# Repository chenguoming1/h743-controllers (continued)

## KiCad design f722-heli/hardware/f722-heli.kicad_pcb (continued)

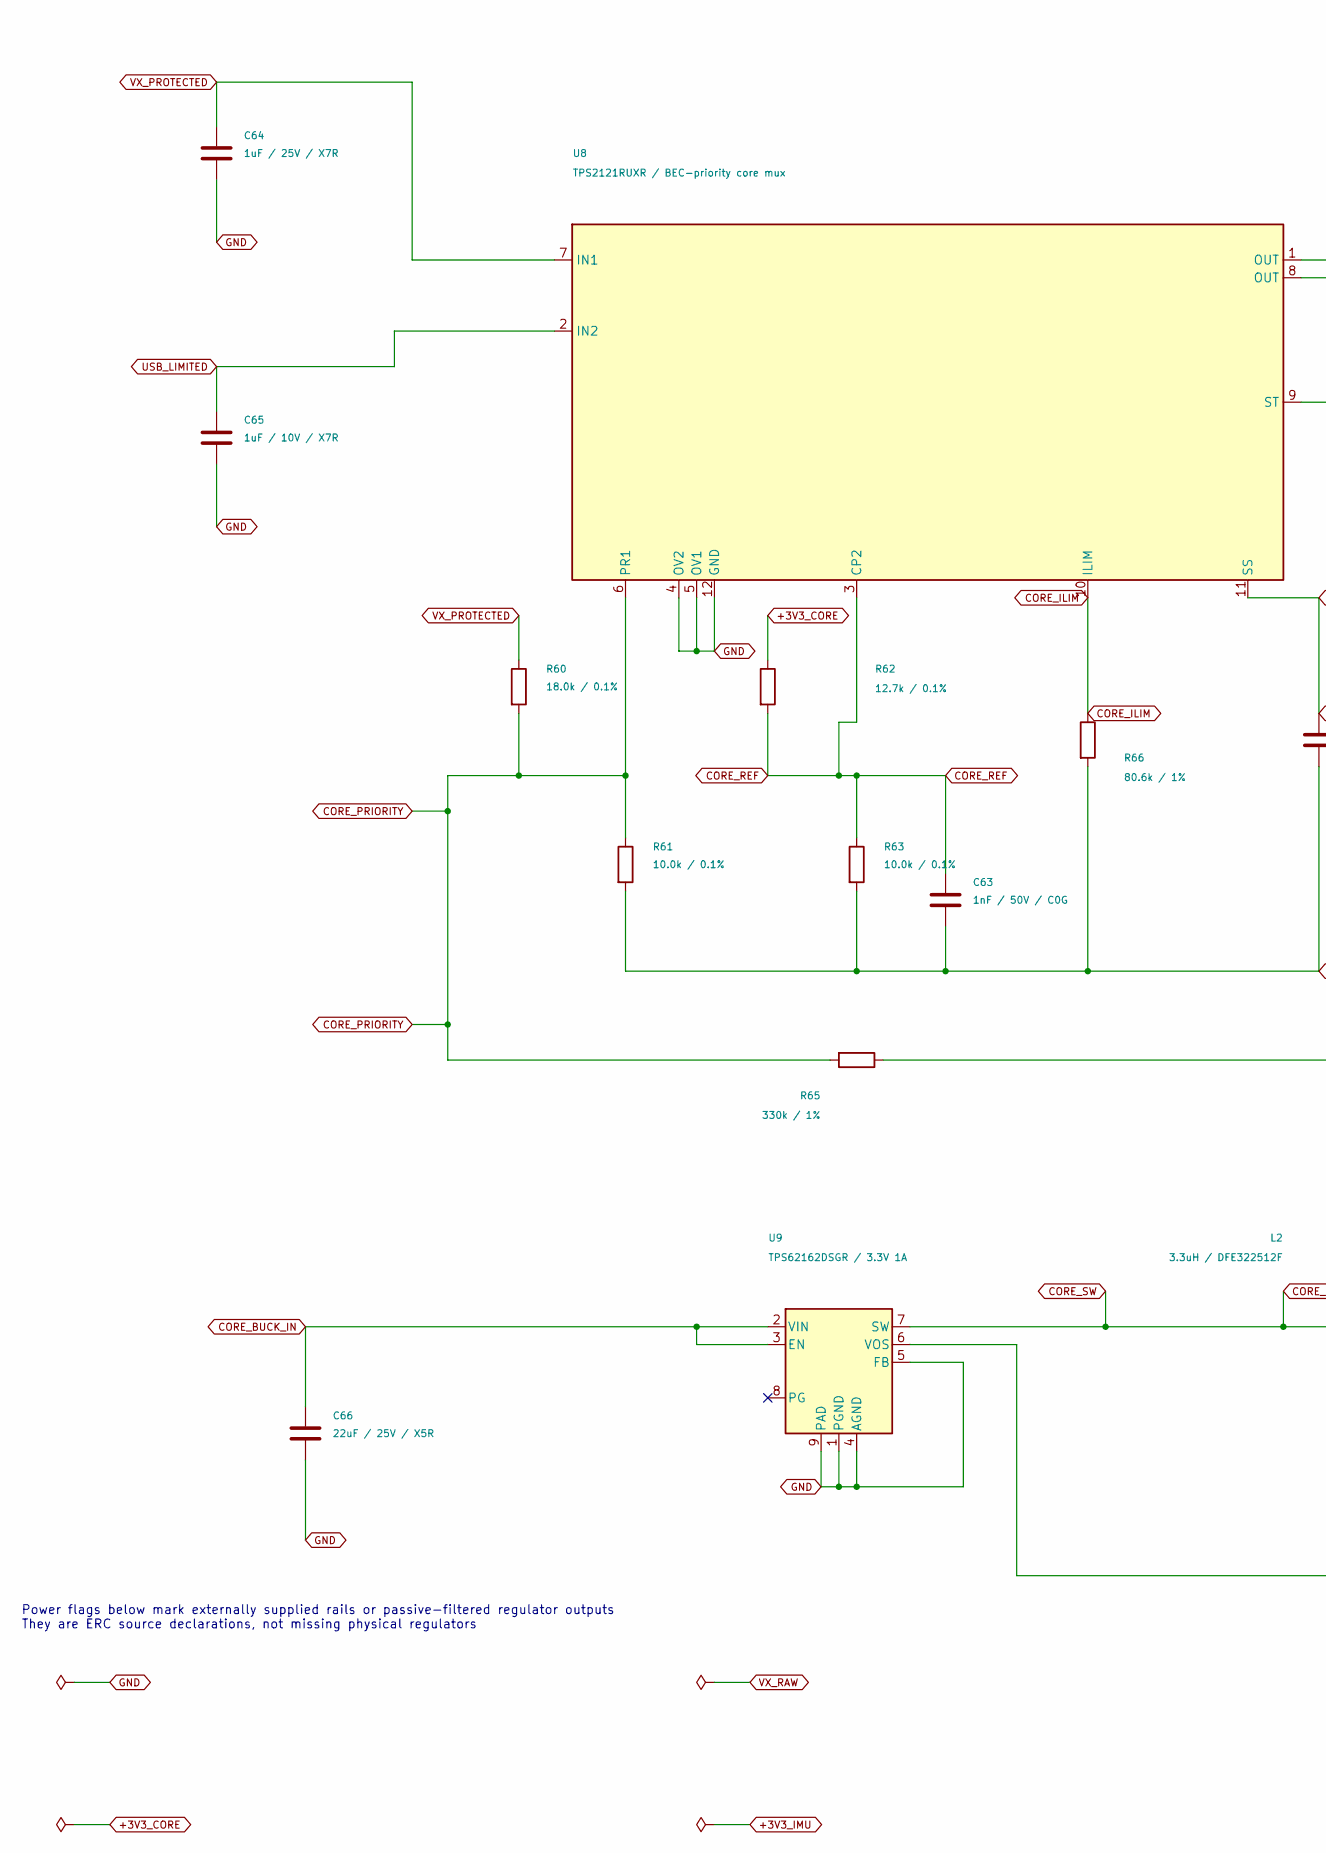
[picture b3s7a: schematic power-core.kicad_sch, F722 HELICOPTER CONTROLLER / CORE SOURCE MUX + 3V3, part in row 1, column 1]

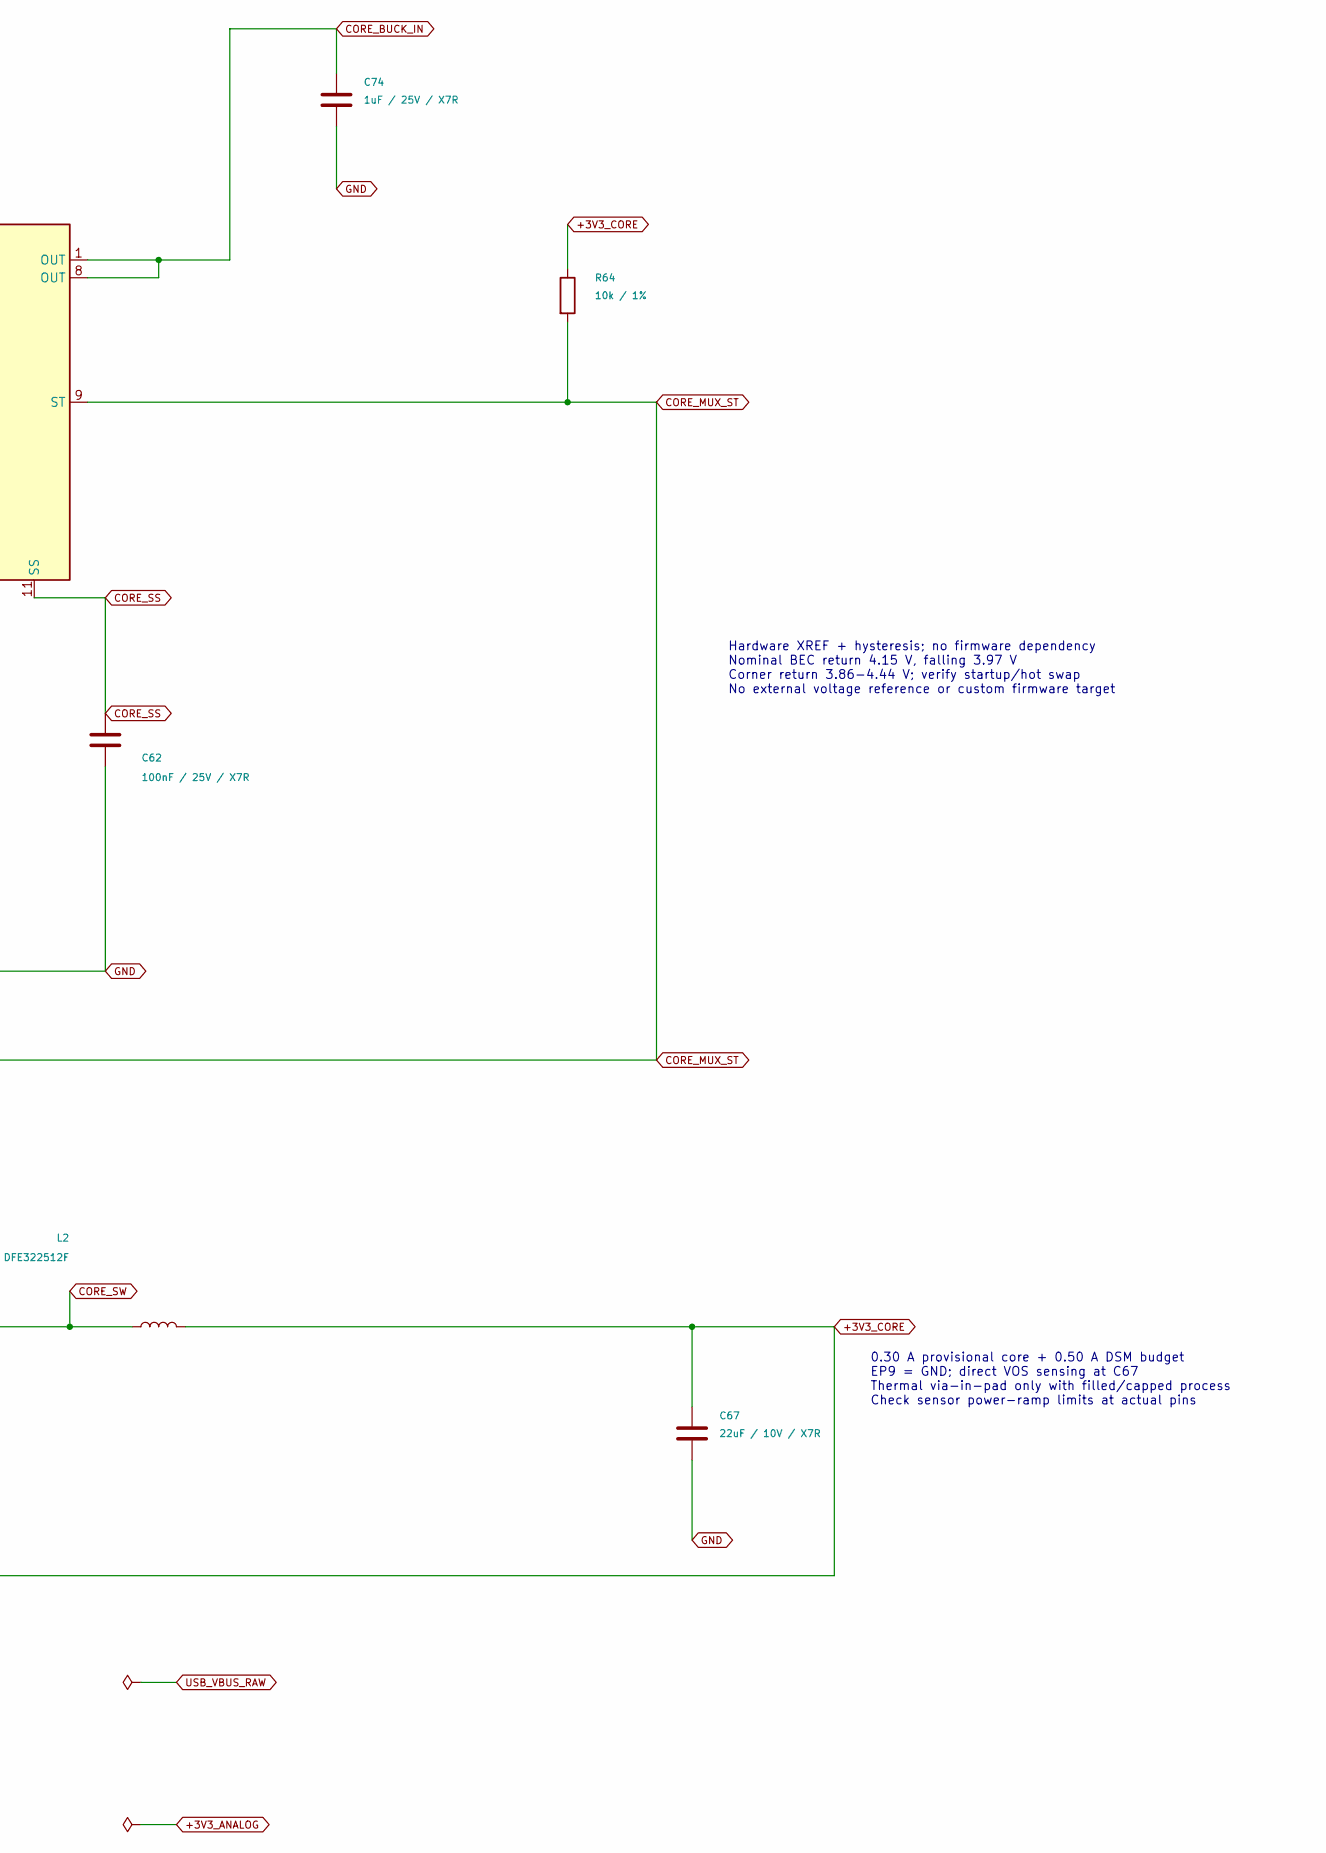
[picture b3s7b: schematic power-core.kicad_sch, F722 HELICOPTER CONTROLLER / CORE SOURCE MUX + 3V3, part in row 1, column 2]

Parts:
C62: 100nF / 25V / X7R; C_0402_1005Metric; MPN CL05B104KA5NNNC; LCSC C155422
C63: 1nF / 50V / C0G; C_0402_1005Metric; MPN CL05C102JB5NNNC; LCSC C307441
C64, C74: 1uF / 25V / X7R; C_0603_1608Metric; MPN CL10B105KA8NNNC; LCSC C29936
C65: 1uF / 10V / X7R; C_0603_1608Metric; MPN CL10B105KP8NNNC; LCSC C95843
C66: 22uF / 25V / X5R; C_0805_2012Metric; MPN GRM21BR61E226ME44L; LCSC C86816
C67: 22uF / 10V / X7R; C_0805_2012Metric; MPN GRM21BZ71A226ME15L; LCSC C907991
L2: 3.3uH / DFE322512F; Murata_DFE322512F; MPN DFE322512F-3R3M=P2; LCSC C3221010
R60: 18.0k / 0.1%; R_0402_1005Metric; MPN RT0402BRD0718KL; LCSC C852579
R61, R63: 10.0k / 0.1%; R_0402_1005Metric; MPN RT0402BRD0710KL; LCSC C190095
R62: 12.7k / 0.1%; R_0402_1005Metric; MPN RT0402BRD0712K7L; LCSC C852509
R64: 10k / 1%; R_0402_1005Metric; MPN 0402WGF1002TCE; LCSC C25744
R65: 330k / 1%; R_0402_1005Metric; MPN 0402WGF3303TCE; LCSC C25778
R66: 80.6k / 1%; R_0402_1005Metric; MPN 0402WGF8062TCE; LCSC C25921
U8: TPS2121RUXR / BEC-priority core mux; Texas_RUX0012A_TPS2121_2x2.5mm; MPN TPS2121RUXR; LCSC C485916
U9: TPS62162DSGR / 3.3V 1A; Texas_DSG0008A_TPS62162_2x2mm_EP0.9x1.6mm; MPN TPS62162DSGR; LCSC C40256

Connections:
+3V3_CORE: C67.1, L2.2, R62.1, R64.1, U9.6 (VOS); also elsewhere on the board
CORE_BUCK_IN: C66.1, C74.1, U8.1 (OUT), U8.8 (OUT), U9.2 (VIN), U9.3 (EN)
CORE_ILIM: R66.1, U8.10 (ILIM)
CORE_MUX_ST: R64.2, R65.1, U8.9 (ST)
CORE_PRIORITY: R60.2, R61.1, R65.2, U8.6 (PR1)
CORE_REF: C63.1, R62.2, R63.1, U8.3 (CP2)
CORE_SS: C62.1, U8.11 (SS)
CORE_SW: L2.1, U9.7 (SW)
GND: C62.2, C63.2, C64.2, C65.2, C66.2, C67.2, C74.2, R61.2, R63.2, R66.2, U8.4 (OV2), U8.5 (OV1), U8.12 (GND), U9.1 (PGND), U9.4 (AGND), U9.5 (FB), U9.9 (PAD); also elsewhere on the board
USB_LIMITED: C65.1, U8.2 (IN2); also elsewhere on the board
VX_PROTECTED: C64.1, R60.1, U8.7 (IN1); also elsewhere on the board

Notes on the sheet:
Hardware XREF + hysteresis; no firmware dependency Nominal BEC return 4.15 V, falling 3.97 V Corner return 3.86-4.44 V; verify startup/hot swap No external voltage reference or custom firmware target
0.30 A provisional core + 0.50 A DSM budget EP9 = GND; direct VOS sensing at C67 Thermal via-in-pad only with filled/capped process Check sensor power-ramp limits at actual pins
Power flags below mark externally supplied rails or passive-filtered regulator outputs They are ERC source declarations, not missing physical regulators

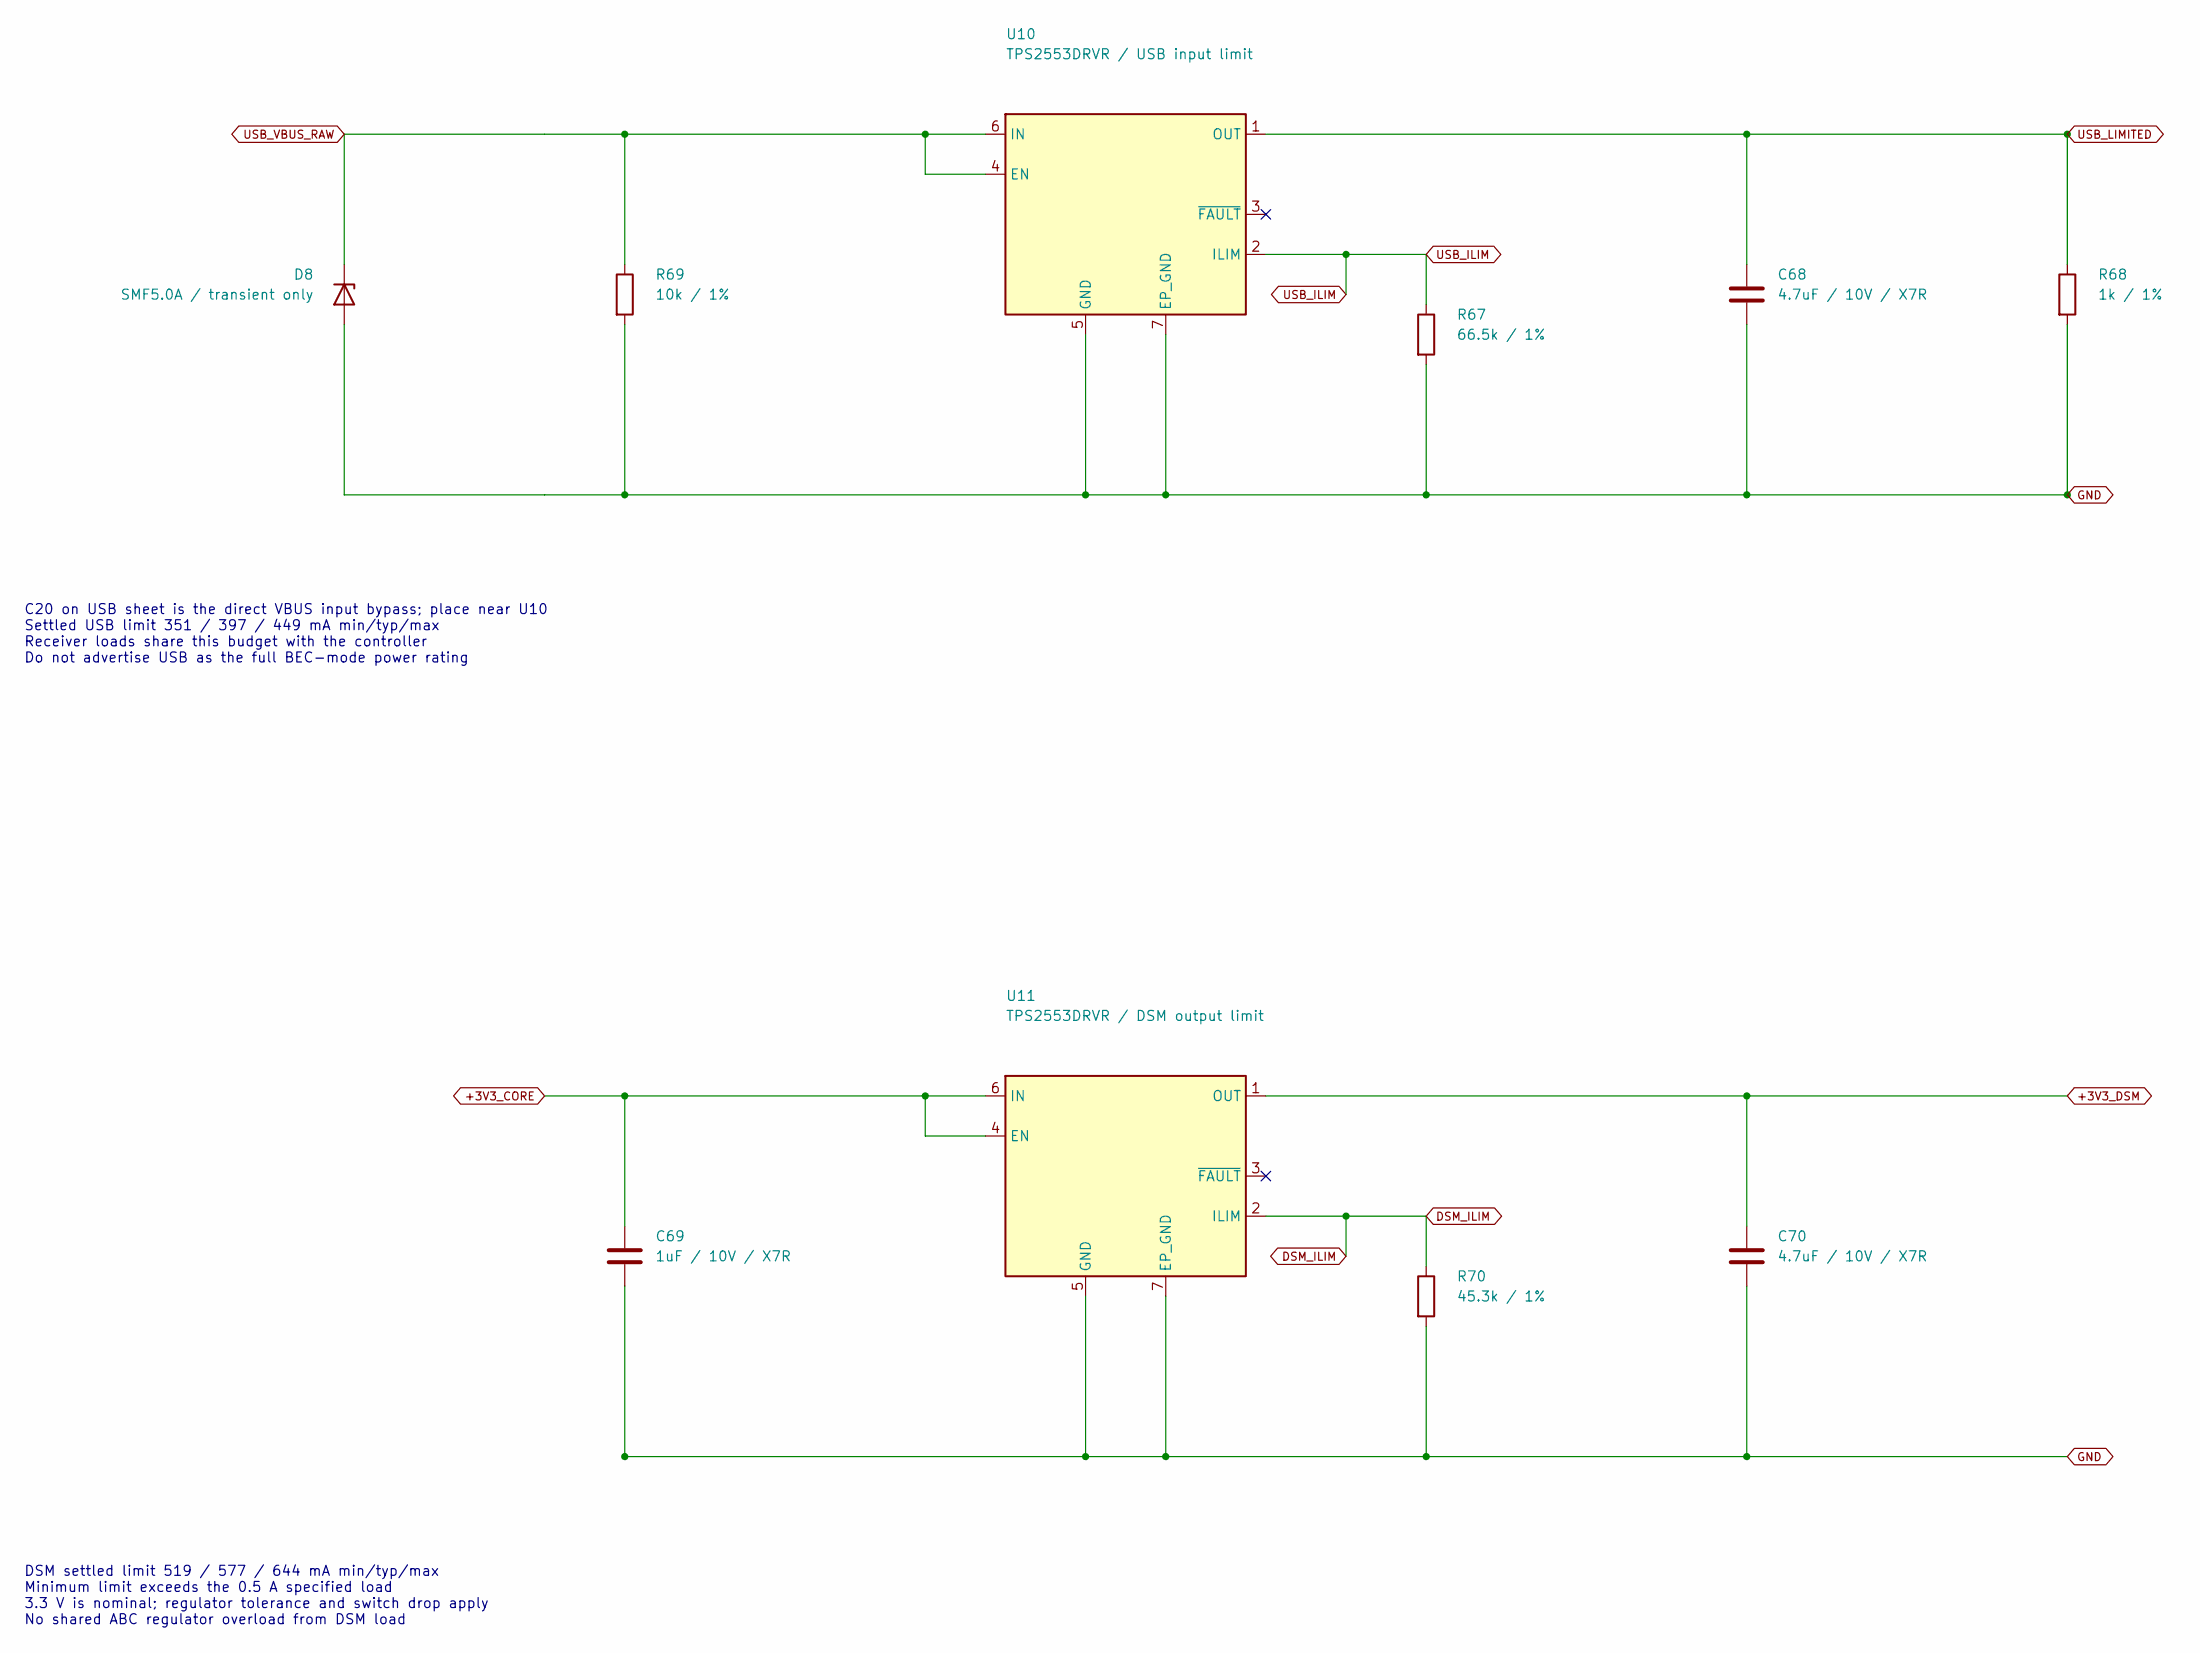
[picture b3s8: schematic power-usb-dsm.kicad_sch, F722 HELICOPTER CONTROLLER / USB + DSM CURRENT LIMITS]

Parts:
C68, C70: 4.7uF / 10V / X7R; C_0603_1608Metric; MPN GRM188Z71A475KE15D; LCSC C913474
C69: 1uF / 10V / X7R; C_0603_1608Metric; MPN CL10B105KP8NNNC; LCSC C95843
D8: SMF5.0A / transient only; Littelfuse_SMF_SOD123FL; MPN SMF5.0A; LCSC C151296
R67: 66.5k / 1%; R_0402_1005Metric; MPN 0402WGF6652TCE; LCSC C29381
R68: 1k / 1%; R_0402_1005Metric; MPN 0402WGF1001TCE; LCSC C11702
R69: 10k / 1%; R_0402_1005Metric; MPN 0402WGF1002TCE; LCSC C25744
R70: 45.3k / 1%; R_0402_1005Metric; MPN 0402WGF4532TCE; LCSC C26980
U10: TPS2553DRVR / USB input limit; Texas_DRV0006A_TPS2553_2x2mm_EP1x1.6mm; MPN TPS2553DRVR; LCSC C138719
U11: TPS2553DRVR / DSM output limit; Texas_DRV0006A_TPS2553_2x2mm_EP1x1.6mm; MPN TPS2553DRVR; LCSC C138719

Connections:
+3V3_CORE: C69.1, U11.4 (EN), U11.6 (IN); also elsewhere on the board
+3V3_DSM: C70.1, U11.1 (OUT); also elsewhere on the board
DSM_ILIM: R70.1, U11.2 (ILIM)
GND: C68.2, C69.2, C70.2, D8.2 (A), R67.2, R68.2, R69.2, R70.2, U10.5 (GND), U10.7 (EP_GND), U11.5 (GND), U11.7 (EP_GND); also elsewhere on the board
USB_ILIM: R67.1, U10.2 (ILIM)
USB_LIMITED: C68.1, R68.1, U10.1 (OUT); also elsewhere on the board
USB_VBUS_RAW: D8.1 (K), R69.1, U10.4 (EN), U10.6 (IN); also elsewhere on the board

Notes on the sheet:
C20 on USB sheet is the direct VBUS input bypass; place near U10 Settled USB limit 351 / 397 / 449 mA min/typ/max Receiver loads share this budget with the controller Do not advertise USB as the full BEC-mode power rating
DSM settled limit 519 / 577 / 644 mA min/typ/max Minimum limit exceeds the 0.5 A specified load 3.3 V is nominal; regulator tolerance and switch drop apply No shared ABC regulator overload from DSM load

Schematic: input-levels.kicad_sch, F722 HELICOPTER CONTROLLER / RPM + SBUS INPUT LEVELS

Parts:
Q1, Q2: BSS138LT1G; SOT-23; MPN BSS138LT1G; LCSC C82045
R36, R37: 4.7k / 1%; R_0402_1005Metric; MPN 0402WGF4701TCE; LCSC C25900
R39, R45: 220R / 1%; R_0402_1005Metric; MPN 0402WGF2200TCE; LCSC C25091
U16: PESD15VS2UT,215 / 15V ESD; SOT-23; MPN PESD15VS2UT,215; LCSC C282556

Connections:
+3V3_CORE: Q1.1 (G), Q2.1 (G), R36.1, R37.1; also elsewhere on the board
GND: U16.3 (COMMON_GND); also elsewhere on the board
RPM_HV: Q1.3 (D), U16.1 (LINE1); also elsewhere on the board
RPM_LV: Q1.2 (S), R36.2, R39.1
SBUS_HV: Q2.3 (D), U16.2 (LINE2); also elsewhere on the board
SBUS_LV: Q2.2 (S), R37.2, R45.1

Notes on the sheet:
External signal -> 470R on port sheet -> HV drain Gate = core supply; source pulled to the same core supply 220R then original MCU node, protected by U13 No fixed inverter; frequency/serial polarity is preserved Stock frequency-input pull-up never sees a VX-level high
Qualify real cable/device edges, startup and powered-off states No extra source capacitor fitted No claim of sustained negative-signal or wrong-output-wiring immunity ESC and tail bidirectional DShot paths remain unbuffered

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
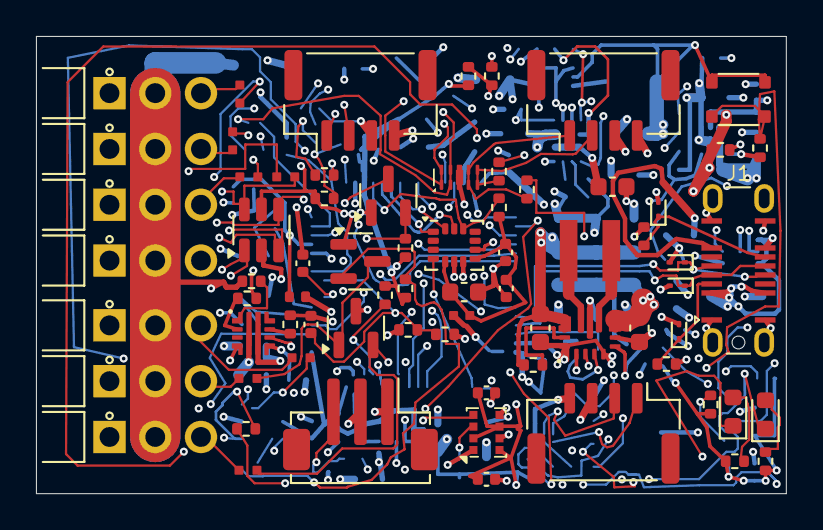
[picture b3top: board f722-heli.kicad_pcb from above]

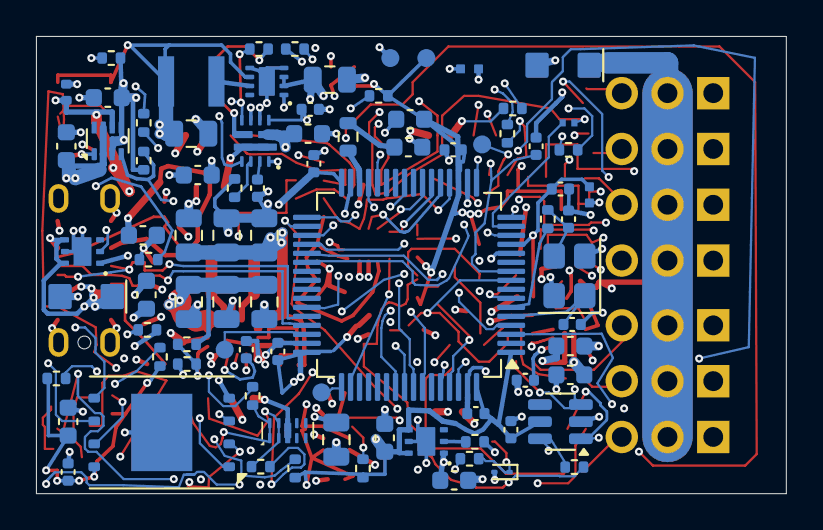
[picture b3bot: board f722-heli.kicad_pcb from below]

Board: 6 copper layers, 41.7 x 25.4 mm, 156 parts (84 on the bottom side), 95 nets.

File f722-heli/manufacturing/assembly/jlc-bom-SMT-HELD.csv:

Comment,Designator,Footprint,LCSC Part #
100nF / 16V / X7R,"C1,C2,C3,C4,C6,C9,C10,C12,C14,C16,C17,C58",F722_Heli:C_0402_1005Metric,C1525
4.7uF / 10V / X5R,C5,F722_Heli:C_0603_1608Metric,C1705
4.7uF / 10V / X7R,"C7,C61,C68,C70",F722_Heli:C_0603_1608Metric,C913474
2.2uF / 10V / X7R(Murata),"C8,C60",F722_Heli:Murata_GRM155Z71A225KE44_0402,C2999759
10nF / 16V / X7R,C11,F722_Heli:C_0402_1005Metric,C318577
2.2uF / 10V / X7R,C13,F722_Heli:C_0603_1608Metric,C100082
1uF / 10V / X7R,"C15,C59,C65,C69",F722_Heli:C_0603_1608Metric,C95843
15pF / 50V / C0G,"C18,C19",F722_Heli:C_0402_1005Metric,C86285
1uF / 16V / X7R,C20,F722_Heli:C_0603_1608Metric,C59782
220nF / 16V / X7R,"C30,C31",F722_Heli:C_0402_1005Metric,C16772
3.3nF / 50V / C0G,C50,F722_Heli:C_0402_1005Metric,C1518207
1uF / 25V / X7R,"C51,C52,C64,C74",F722_Heli:C_0603_1608Metric,C29936
22uF / 25V / X5R,"C53,C54,C66,C71",F722_Heli:C_0805_2012Metric,C86816
47uF / 10V / X5R,"C55,C56,C57,C75",F722_Heli:C_0805_2012Metric,C124129
100nF / 25V / X7R,C62,F722_Heli:C_0402_1005Metric,C155422
1nF / 50V / C0G,C63,F722_Heli:C_0402_1005Metric,C307441
22uF / 10V / X7R,C67,F722_Heli:C_0805_2012Metric,C907991
10uF / 25V / X5R / HF,"C72,C73",F722_Heli:C_0603_1608Metric,C386081
GREEN,D1,F722_Heli:LED_0603_1608Metric,C2289
RED,D2,F722_Heli:LED_0603_1608Metric,C2286
ESD9M5.0ST5G,"D3,D4,D5,D6,D7",F722_Heli:D_SOD-923,C242267
SMF5.0A / transient only,D8,F722_Heli:Littelfuse_SMF_SOD123FL,C151296
SMF15CA / bidirectional,D9,F722_Heli:Littelfuse_SMF_SOD123FL,C1851361
600R@100MHz / 0.3A,"FB1,FB2",F722_Heli:Murata_BLM15AG_0402,C76884
USB4145-03-0170-C,J1,F722_Heli:USB_C_Receptacle_GCT_USB4145-03-0170-C_16P_Vertical,C5181332
PORT A / JST GH,J9,F722_Heli:JST_GH_BM04B-GHS-TBT_1x04-1MP_P1.25mm_Vertical,C161692
PORT B / JST GH,J10,F722_Heli:JST_GH_BM04B-GHS-TBT_1x04-1MP_P1.25mm_Vertical,C161692
PORT C / JST GH,J11,F722_Heli:JST_GH_BM04B-GHS-TBT_1x04-1MP_P1.25mm_Vertical,C161692
DSM / JST ZH,J12,F722_Heli:JST_ZH_B3B-ZR-SM4-TF_1x03-1MP_P1.50mm_Vertical,C489717
1.5uH / XGL4020-152MEC,L1,F722_Heli:Coilcraft_XGL4020,C7417180
3.3uH / DFE322512F,L2,F722_Heli:Murata_DFE322512F,C3221010
BSS138LT1G,"Q1,Q2",F722_Heli:SOT-23,C82045
10k / 1%,"R1,R3,R4,R6,R64,R69",F722_Heli:R_0402_1005Metric,C25744
2.2k / 1%,"R2,R10,R11",F722_Heli:R_0402_1005Metric,C25879
10k / 1%,R5,F722_Heli:R_0402_1005Metric_R5_ClearPin1Silk,C25744
4.7k / 1%,"R7,R8,R36,R37",F722_Heli:R_0402_1005Metric,C25900
0R / drive tuning,R9,F722_Heli:R_0402_1005Metric,C17168
5.1k / 1%,"R14,R15",F722_Heli:R_0402_1005Metric,C25905
0.12R / 1% / VCAP ESR,R16,F722_Heli:R_Panasonic_ERJ3R_0603,C4059772
470R / 1% / 0.20W,"R20,R21,R22,R23,R24,R25,R26",F722_Heli:Panasonic_ERJPA2_0402,C427238
22R / 1%,"R30,R32,R33,R34,R35,R38",F722_Heli:R_0402_1005Metric,C25092
22R / 1%,R31,F722_YAGEO:R_0201_0603Metric_YAGEO_AC,C144830
220R / 1%,"R39,R45",F722_Heli:R_0402_1005Metric,C25091
105k / 0.1%,R40,F722_Heli:R_0402_1005Metric,C2984407
20.0k / 0.1%,R41,F722_Heli:R_0402_1005Metric,C705630
68.0k / 0.1%,R42,F722_Heli:R_0402_1005Metric,C5266108
16.0k / 0.1%,"R43,R44",F722_Heli:R_0402_1005Metric,C513647
1.5M / 1%,R50,F722_Heli:R_0402_1005Metric,C22276
390k / 1%,R51,F722_Heli:R_0402_1005Metric,C25782
750R / 1%,R52,F722_Heli:R_0402_1005Metric,C25132
4.7k / 1%,R53,F722_Heli:Panasonic_ERJPA2_0402,C427244
53.6k / 0.1%,R54,F722_Heli:R_0402_1005Metric,C852835
10.0k / 0.1%,"R55,R61,R63",F722_Heli:R_0402_1005Metric,C190095
100k / 1%,"R56,R57",F722_Heli:R_0402_1005Metric,C25741
47k / 1%,R58,F722_Heli:R_0402_1005Metric,C25792
18.0k / 0.1%,R60,F722_Heli:R_0402_1005Metric,C852579
12.7k / 0.1%,R62,F722_Heli:R_0402_1005Metric,C852509
330k / 1%,R65,F722_Heli:R_0402_1005Metric,C25778
80.6k / 1%,R66,F722_Heli:R_0402_1005Metric,C25921
66.5k / 1%,R67,F722_Heli:R_0402_1005Metric,C29381
1k / 1%,R68,F722_Heli:R_0402_1005Metric,C11702
45.3k / 1%,R70,F722_Heli:R_0402_1005Metric,C26980
100k / 1% / ROM RX idle,R71,F722_Heli:R_0402_1005Metric,C25741
BOOT / KMT031NGJLHS,SW1,F722_Heli:CK_KMT031NGJLHS,C221708
STM32F722RET6,U1,F722_Heli:LQFP-64_10x10mm_P0.5mm,C118207
ICM-42688-P,U2,F722_Heli:LGA-14_3x2.5mm_P0.5mm_LayoutBorder3x4y,C1850418
W25N01GVZEIG / 128MiB,U3,F722_Heli:WSON-8-1EP_8x6mm_P1.27mm_EP3.4x4.3mm,C88868
DPS368XTSA1 / 0x76,U4,F722_Heli:Infineon_DPS368_VLGA-8_2.5x2mm_SMD,C3232508
TPS259472ARPWR,U5,F722_Heli:Texas_RPW0010A_TPS259472_2x2mm,C3662789
TPS63070RNMR / nominal 5.088V,U6,F722_Heli:Texas_RNM0015A_TPS63070_2.5x3mm,C109322
TPS2117DRLR / ABC priority mux,U7,F722_Heli:SOT-583-8,C22399676
TPS2121RUXR / BEC-priority core mux,U8,F722_Heli:Texas_RUX0012A_TPS2121_2x2.5mm,C485916
TPS62162DSGR / 3.3V 1A,U9,F722_Heli:Texas_DSG0008A_TPS62162_2x2mm_EP0.9x1.6mm,C40256
TPS2553DRVR / USB input limit,U10,F722_Heli:Texas_DRV0006A_TPS2553_2x2mm_EP1x1.6mm,C138719
TPS2553DRVR / DSM output limit,U11,F722_Heli:Texas_DRV0006A_TPS2553_2x2mm_EP1x1.6mm,C138719
USBLC6-4SC6 / header clamp,"U12,U13",F722_Heli:SOT-23-6,C111212
TPD4E05U06DQAR / UART ESD,"U14,U15",F722_Heli:Texas_DQA0010B_TPD4E05U06_2.5x1mm,C138714
"PESD15VS2UT,215 / 15V ESD",U16,F722_Heli:SOT-23,C282556
8MHz / CL10pF / TAXM8M4RDBCCT2T,Y1,F722_Heli:Crystal_SMD_3225-4Pin_3.2x2.5mm,C400090

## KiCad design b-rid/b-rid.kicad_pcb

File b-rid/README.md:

# B-RID engineering prototype

Editable KiCad 10 project for a compact, battery-powered Broadcast Remote ID hardware prototype with onboard GNSS, USB-C charging/programming, a corner power switch and G/R/S indicators.

**Status: engineering CAD completed for review; fabrication and battery connection are not released.** The final native schematic/PCB checks and remaining qualification gates are recorded in `review/`. No firmware, flashing, RF compliance, flight approval or production-readiness claim is included.

**Current routing update:** VSYS bridges are simplified/widened, all remaining route widths are reviewed, redundant fragments are merged, the VBUS input feed is widened, and tested USB differential-pair rules are active. Fresh native checks are 0/0/0/0. See [review/CURRENT_REVISION.md](review/CURRENT_REVISION.md) for current hashes, before/after views and all eight regression checks. Older review artifacts retain their original revision context.

## Current hardware

- Six layers, 35 × 24 mm nominal populated plan envelope; height unrestricted; parts on both faces
- ESP32-C3-MINI-1-N4X integrated antenna over a recessed PCB outline, inside the rectangular plan envelope
- u-blox MIA-M10Q-00B receiver with a directly mounted INPAQ PA1575MQ4S-123-1Z ceramic patch; no antenna cable
- JLC06161H-3313 impedance basis: 0.135 mm / 0.150 mm USB pair, and 0.150 mm GNSS feed, with a 0.300 mm minimum outer GND-zone clearance; both coplanar and non-coplanar calculator results were checked
- BQ24074 power-path charger and TPS63031 3V3 converter, with revised local capacitor/switching loops and exact capacitor selections supported by manufacturer DC-bias data
- TMUX1119 battery-sense isolation prevents the powered battery divider from driving an unpowered ESP input
- G and R use green LEDs driven by future GNSS-fix/RID-transmission firmware state. S-green shows enabled 3V3 power; S-red shows charging and can work with system power off
- Patch and G/R/S indicators on the SKY-marked B face; both RF modules on F for one final module reflow pass
- 60 footprint references: 4 test pads and 56 model references. C13/C14 are intentionally unpopulated RF tuning positions

Open `b-rid.kicad_pro`. Local symbols, custom footprints and all referenced 3D model files are included. The PCB is editable without running generators. Existing historical scripts are not needed to open or edit the project.

## Read before fabrication

1. Select and qualify an exact protected cell, temperature sensor and keyed 3-wire harness. Charge temperature limits, current/pulse capability, charge-voltage tolerance and safety-timer behavior remain unresolved. Do not attach a generic LiPo merely because its connector fits
2. Confirm exact MIA-M10Q and INPAQ antenna supply, assembly process and first-article fit. Public stock for the exact GNSS receiver/antenna was not qualified
3. Have the fabricator confirm the stated stackup, finished copper/impedance and filled/capped via-in-pad process. Review the manufacturing data before production
4. Validate GNSS matching/acquisition/coexistence, USB signal integrity/ESD and power/startup/thermal behavior on prototypes
5. Implement and test firmware. USB SOF detection alone does not establish a 500 mA current grant; MCU-off host-suspend detection remains unresolved

The package intentionally separates design checks from supplier and bench gates. It contains the current editable project and actual renders, not an order-ready CAM release. See `review/ENGINEERING_CHECKS.md`, `review/FIRMWARE_INTERFACE.md`, `review/ASSEMBLY_NOTES.md` and `review/PROTOTYPE_GATES.md`.

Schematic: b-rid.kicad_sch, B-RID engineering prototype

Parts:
A1: INPAQ PA1575MQ4S-123-1Z; INPAQ_PA1575MQ4S_10x10_Pin; MPN PA1575MQ4S-123-1Z
C1, C8: 2.2u/50V X5R; C_0603_1608Metric; MPN GRM188R61H225KE11D; LCSC C162273
C2, C3, C4, C10: 10u/50V X5R; C_0805_2012Metric; MPN GRM21BR61H106KE43L; LCSC C440198
C5, C9, C11, C15, C16, C17: 100n/16V X7R; C_0402_1005Metric; MPN GRM155R71C104KA88D; LCSC C71629
C6, C7: 22u/16V X5R; C_0805_2012Metric; MPN GRM21BR61C226ME44L; LCSC C86817
C12: 1u/10V X5R EN; C_0402_1005Metric; MPN GRM155R61A105KE15D; LCSC C76999
C13, C14: DNP RF match; C_0201_0603Metric; MPN DNP; not fitted
D1: APHB1608CGKSURKC G GNSS state; LED_APHB1608CGKSURKC; MPN APHB1608CGKSURKC; LCSC C6506245
D2: APHB1608CGKSURKC R RID state; LED_APHB1608CGKSURKC; MPN APHB1608CGKSURKC; LCSC C6506245
D3: APHB1608CGKSURKC S POWER / CHARGE; LED_APHB1608CGKSURKC; MPN APHB1608CGKSURKC; LCSC C6506245
J1: USB-C; USB_C_Receptacle_HRO_TYPE-C-31-M-12; MPN TYPE-C-31-M-12
J2: 1S protected pack + NTC; JST_SH_SM03B-SRSS-TB_1x03-1MP_P1.00mm_Horizontal; MPN SM03B-SRSS-TB(LF)(SN)
L1: 1.5uH WE-MAPI 74438334015; L_Wuerth_MAPI-3012; MPN 74438334015
Q1: 2N7002P charge isolation; SOT-23; MPN 2N7002P,215; LCSC C81488
R1, R2: 5.1k; R_0402_1005Metric
R3, R4: 22R; R_0201_0603Metric
R5: 5.90k / 150mA; R_0402_1005Metric
R6: 3.09k ILIM; R_0402_1005Metric
R7, R10: 100k; R_0402_1005Metric
R8, R9: 10k; R_0402_1005Metric
R11: 10k EN; R_0402_1005Metric
R12: 10k IO2; R_0402_1005Metric
R13: 1M; R_0402_1005Metric
R14: 330k; R_0402_1005Metric
R15: 0R RF series; R_0201_0603Metric
R16: 0R reserved; R_0402_1005Metric
R18: 0R RTC_O; R_0402_1005Metric
R19, R20, R21: 1k LED ~1.2mA; R_0402_LED_NoSilk
R22: 3.3k CHARGE ~0.9mA; R_0402_1005Metric
R23: 100k CHG pull-up; R_0402_1005Metric
R24: 100k USB suspend default; R_0201_0603Metric
R25: 10k GPIO8 boot strap; R_0201_0603Metric
SW1: POWER slide; SW_SPDT_Shouhan_MSK12C02; MPN MSK12C02; LCSC C431540
TP1: GND; TestPoint_Pad_D1.0mm
TP2: ESP_EN; TestPoint_Pad_D1.0mm
TP3: BOOT_IO9; TestPoint_Pad_D1.0mm
TP4: 3V3; TestPoint_Pad_D1.0mm
U1: ESP32-C3-MINI-1-N4X; ESP32-C3-MINI-1; MPN ESP32-C3-MINI-1-N4X
U2: MIA-M10Q-00B; ublox_LGA-53_4.5x4.5mm_Layout9x9_P0.5mm; MPN MIA-M10Q-00B
U3: BQ24074RGT; BQ24074_RGT0016B_TI; MPN BQ24074RGTR
U4: TPS63031DSK; TPS63031_DSK0010A_TI; MPN TPS63031DSKR
U5: USBLC6-2SC6; SOT-23-6; MPN USBLC6-2SC6; LCSC C7519
U6: TMUX1119DCKR; SOT-363_SC-70-6; MPN TMUX1119DCKR

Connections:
/3V3: C6.1, C7.1, C8.1, C9.1, C10.1, C11.1, R8.1, R9.1, R11.1, R12.1, R21.1, R25.1, TP4.1, U1.3 (3V3), U2.B1 (VCC), U2.J4 (V_IO), U4.1 (VOUT), U4.10 (FB), U6.1 (SEL)
/BAT+: C3.1, J2.1, R13.1, U3.2 (BAT), U3.3 (BAT)
/BATT_NTC: J2.2, U3.1 (TS)
/BAT_DIV: C16.1, R13.2, R14.1, U6.6 (S2)
/BAT_SENSE: U1.13 (IO1), U6.5 (D)
/BOOT_IO9: TP3.1, U1.23 (IO9)
/BUCK_EN: R10.1, SW1.1 (A), U4.6 (EN)
/CC1: J1.A5 (CC1), R1.1
/CC2: J1.B5 (CC2), R2.1
/CHARGE_ACTIVE: Q1.3 (D), R8.2, U1.19 (IO5)
/CHG_N: D3.4 (K2), Q1.1 (G), R23.2, U3.9 (~CHG)
/ESP_EN: C12.1, R11.2, TP2.1, U1.8 (EN)
/GNSS_RX: U1.31 (TXD0), U2.H1 (RX)
/GNSS_TX: U1.30 (RXD0), U2.G1 (TX)
/ILIM: R6.1, U3.12 (ILIM)
/ISET: R5.1, U3.16 (ISET)
/L1: L1.1, U4.4 (L1)
/L2: L1.2, U4.2 (L2)
/LED_CHG_A: D3.3 (A2), R22.2
/LED_G: R19.1, U1.20 (IO6)
/LED_G_A: D1.1 (A1), R19.2
/LED_R: R20.1, U1.21 (IO7)
/LED_R_A: D2.1 (A1), R20.2
/LED_S_A: D3.1 (A1), R21.2
/PGOOD_N: R9.2, U1.18 (IO4), U3.7 (~PGOOD)
/RES_F9: R16.1, U2.F9 (Reserved)
/RES_PAIR: U2.D2 (Reserved), U2.E2 (Reserved)
/RF_ANT: A1.1, C14.1, R15.2
/RF_IN: C13.1, R15.1, U2.B9 (RF_IN)
/RTC_UNUSED: R18.1, U2.A5 (RTC_O)
/STRAP_IO2: R12.2, U1.5 (IO2)
/STRAP_IO8: R25.2, U1.22 (IO8)
/USB_500_EN: R7.1, U1.12 (IO0), U3.6 (EN1)
/USB_D_CONN_N: J1.A7 (D-), J1.B7 (D-), R4.1, U5.3 (I/O2), U5.4 (I/O2)
/USB_D_CONN_P: J1.A6 (D+), J1.B6 (D+), R3.1, U5.1 (I/O1), U5.6 (I/O1)
/USB_D_N: R4.2, U1.26 (IO18/USB_D-)
/USB_D_P: R3.2, U1.27 (IO19/USB_D+)
/USB_SUSPEND: R24.1, U1.6 (IO3), U3.5 (EN2)
/VBUS: C1.1, C15.1, J1.A4 (VBUS), J1.A9 (VBUS), J1.B4 (VBUS), J1.B9 (VBUS), R22.1, R23.1, U3.13 (IN), U5.5 (VBUS)
/VSYS: C2.1, C4.1, C5.1, C17.1, SW1.2 (B), U3.10 (OUT), U3.11 (OUT), U4.5 (VIN), U4.8 (VINA), U6.2 (VDD)
GND: C1.2, C2.2, C3.2, C4.2, C5.2, C6.2, C7.2, C8.2, C9.2, C10.2, C11.2, C12.2, C13.2, C14.2, C15.2, C16.2, C17.2, D1.2 (K1), D2.2 (K1), D3.2 (K1), J1.A1 (GND), J1.A12 (GND), J1.B1 (GND), J1.B12 (GND), J1.SH (SHIELD), J2.3, Q1.2 (S), R1.2, R2.2, R5.2, R6.2, R7.2, R10.2, R14.2, R16.2, R18.2, R24.2, TP1.1, U1.1 (GND), U1.2 (GND), U1.11 (GND), U1.14 (GND), U1.36 (GND), U1.37 (GND), U1.38 (GND), U1.39 (GND), U1.40 (GND), U1.41 (GND), U1.42 (GND), U1.43 (GND), U1.44 (GND), U1.45 (GND), U1.46 (GND), U1.47 (GND), U1.48 (GND), U1.49 (GND), U1.50 (GND), U1.51 (GND), U1.52 (GND), U1.53 (GND), U2.A1 (GND), U2.A2 (GND), U2.A3 (GND), U2.A8 (GND), U2.A9 (GND), U2.B2 (GND), U2.B8 (GND), U2.C3 (GND), U2.C9 (GND), U2.E3 (GND), U2.E4 (GND), U2.E9 (GND), U2.F1 (GND), U2.F3 (GND), U2.F4 (GND), U2.G3 (GND), U2.G4 (GND), U2.G5 (GND), U2.G6 (GND), U2.G7 (Reserved), U2.H8 (GND), U2.J8 (GND), U2.J9 (GND), U3.4 (~CE), U3.8 (VSS), U3.17 (VSS), U4.3 (PGND), U4.7 (PS/SYNC), U4.9 (GND), U4.11 (PGND), U5.2 (GND), U6.3 (GND), U6.4 (S1)

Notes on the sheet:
G/R indicators require future firmware. An illuminated R is not proof of compliant RF/RID transmission.
Default 100mA. SOF/connected is NOT a configured 500mA grant. Validate host grant before selecting USB500.
USB-C / 5 V INPUT / CC / DATA
USB defaults to 100 mA input limit; firmware may select 500 mA after enumeration.
Protected 1S pack with 10k NTC required; charge ~150 mA is provisional.
INPAQ 10x10x4mm GPS L1 patch; engineered through-pin mount. Final RF tuning and exact-part sourcing required.
POWER-OFF ADC ISOLATION / USB POLICY / RECOVERY STRAP
3.3 V BUCK-BOOST
1S LI-ION CHARGE + POWER PATH
U6: SEL=3V3. Off -> ADC grounded; on -> BAT_DIV. C16 stays on divider side. Verify rail-collapse sequencing.
Q1 prevents the VBUS-powered CHG node from driving an unpowered ESP input. Charging = (PGOOD_N low) AND (CHARGE_ACTIVE high); ignore CHARGE_ACTIVE without valid USB input.
GPIO8 pull-up supports manual download with GPIO9/BOOT low. No status LED on strapping pins.
Native CAD checks passed; battery, sourcing, assembly and physical qualification pending.
USB EN2/EN1: 00=100mA, 01=500mA, 11=suspend. Enter EN1 first; resume EN2 first. Avoid 10 ILIM state.
Charger EN2: GPIO3. S-green shows enabled system rail; G/R use GPIO6/GPIO7 firmware state.
STATUS INDICATORS / ISOLATED CHARGE SENSE
S green: 3V3 system rail enabled (not firmware-health proof). S red: charger CHG_N low, independent of MCU power. Charging can show amber while running.
G: GPIO6, blink acquiring / steady valid GNSS. R: GPIO7, actual successful RID transmit state.
MCU-off charging cannot detect host suspend. USB power policy and prototype measurements remain release gates.
ESP antenna is inside overall outline with host-board corner recess and all-layer keepout.
ESP32-C3 BLE/WI-FI + PROGRAMMING
MIA GNSS + DIRECT CERAMIC PATCH / RF MATCH

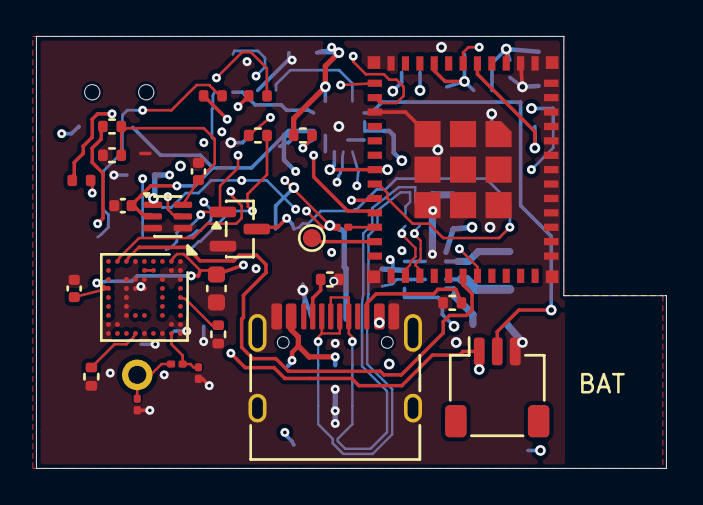
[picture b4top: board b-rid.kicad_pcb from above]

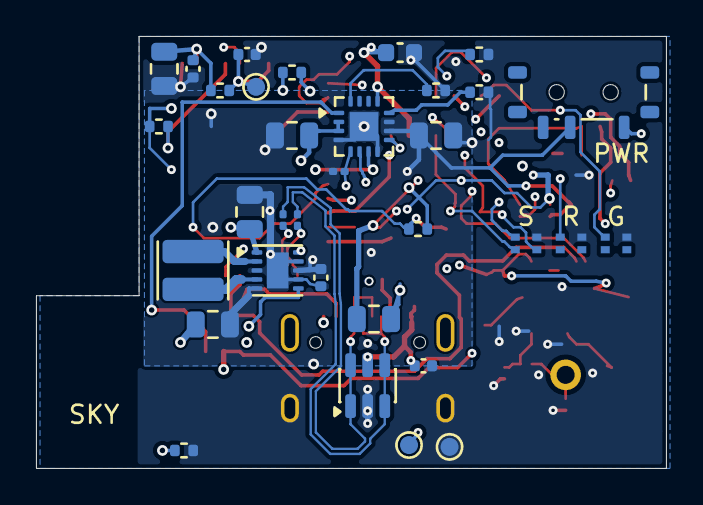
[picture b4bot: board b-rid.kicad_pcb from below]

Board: 6 copper layers, 35.0 x 24.0 mm, 60 parts (34 on the bottom side), 41 nets.
